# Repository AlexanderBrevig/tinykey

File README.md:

# tinykey

A project just for fun, to see if I can type on it.

## The rough idea

The layout:

```
↑ ◐ ● ◑ ↹ ⌫      ↩ ␣ ◐ ● ◑ ↓
```

Imagine mapping the home row `ASDFG` to three keys, using chords.
Let's say we only have the `SDF` keys, the mapping will be like this:

```
S = A
SD = S
D = D
DF = F
F = G
```

So, if you wanted to type `SAD` then you would press `SD` `S` `D`. The grouped keys becomes a chord for your ring and middle finger.
Now then, what if you wanted to type `FEAST`?

Notice that `↑` on the pinky? It shifts the home row up.
Before things get crazy, let's rename `SDF` to `◐●◑`.

Now, then `FEAST` becomes:

```
F  E  A S  T
●◑ ↑● ● ◐● ↑◑ 
```

The same applies for the `↓` on the right pinky. This shifts the home row down.

So what about the thumbs then?

The left thumb has two keys, a TAB `↹` and a BACKSPACE `⌫`. 
The right thumb has RETURN `↩` and SPACE `␣`.
However, when held they enter other layers.

In my (still only slideware) config, I've mapped the numbers to the top row on the SPACE layer.
So, for me to type out `1337` it would be:

```
1   3   3   7
↑◐␣ ↑●␣ ↑●␣ ↑␣●◑
```

I will post my complete keymap when it's ready.

## Taking it further

We could also realize five keys by using timing and only two keys.

```
A S   D  F   G
◐ ◐-◑ ◑◐ ◑-◐ ◑
```

S and F has a roll, while D is _at the same time_ (within a confurable Δt ms).

Will try to play with this as well, and thus getting the layout down to 10 keys total.

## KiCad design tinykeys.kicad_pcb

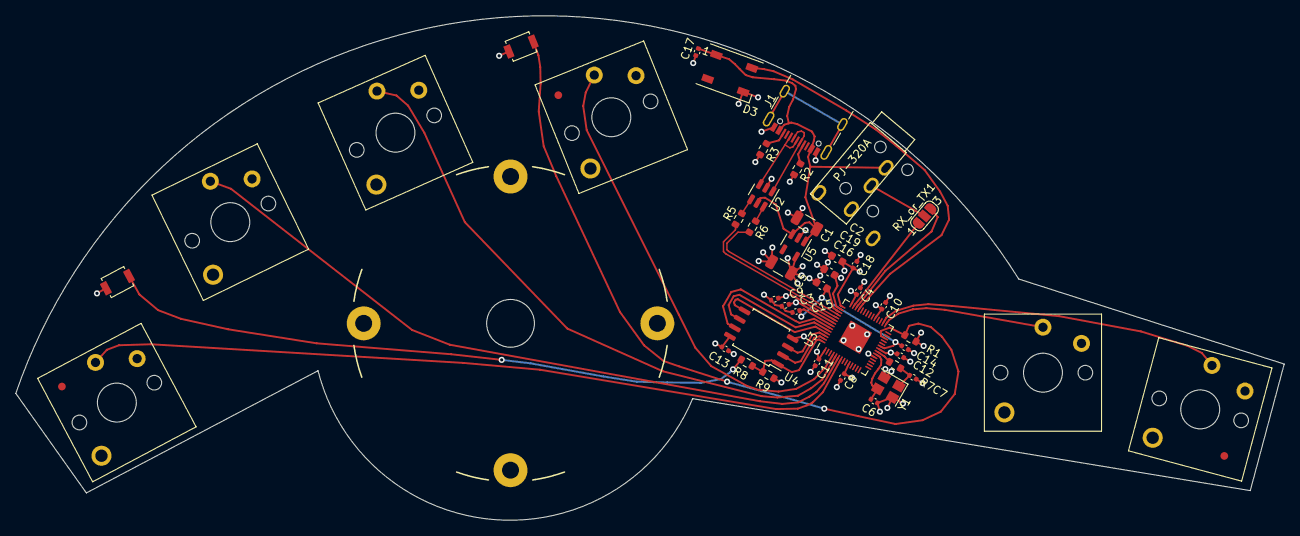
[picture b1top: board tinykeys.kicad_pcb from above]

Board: 4 copper layers, 164.6 x 65.4 mm, 48 parts (0 on the bottom side), 33 nets.

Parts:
BOOT1: TACT; SW_SPST_B3U-1000P
C1: DNP; C_1206_3216Metric
C2, C16, C19: 1u; C_0603_1608Metric
C3, C4, C8, C9, C10, C11, C12, C13, C14, C15, C17, C18: 100n; C_0402_1005Metric
C5: 1u; C_1206_3216Metric
C6, C7: 15p; C_0402_1005Metric
D3: WS2812B; LED_WS2812B_PLCC4_5.0x5.0mm_P3.2mm
FID1, FID2, FID3: Fiducial; dualfiducial
H1: MountingHole_Pad; Tenting_Puck
INDEX1: SW; SW_Kailh_Choc_V1V2_1.00u
J1: USB_C_Receptacle_USB2.0; USB_C_Receptacle_GCT_USB4105-xx-A_16P_TopMnt_Horizontal
J2: AudioJack4; TRRS-PJ-320A
MIDDLE1: SW; SW_Kailh_Choc_V1V2_1.00u
PINKY1: SW; SW_Kailh_Choc_V1V2_1.00u
R1, R9: 10k; R_0603_1608Metric
R2, R3: 5K1; R_0603_1608Metric
R5, R6: 27R; R_0603_1608Metric
R7, R8: 1k; R_0603_1608Metric
RESET1: TACT; SW_SPST_B3U-1000P
RING1: SW; SW_Kailh_Choc_V1V2_1.00u
RX_or_TX1: Jumper_3_Open; SolderJumper-3_P1.3mm_Open_RoundedPad1.0x1.5mm_NumberLabels
TFAR1: SW; SW_Kailh_Choc_V1V2_1.00u
TNEAR1: SW; SW_Kailh_Choc_V1V2_1.00u
U2: USBLC6-2SC6; SOT-23-6
U3: RP2040; QFN-56-1EP_7x7mm_P0.4mm_EP3.2x3.2mm
U4: W25Q128JVS; SOIC-8_5.23x5.23mm_P1.27mm
U5: TLV70033DDCR; SOT-23-5
Y1: 12MHz; Crystal_SMD_3225-4Pin_3.2x2.5mm

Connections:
+1V1: C14.1, C15.1, C16.1, U3.23 (DVDD), U3.45 (VREG_VOUT), U3.50 (DVDD)
+3V3: C2.1, C3.1, C4.1, C5.1, C8.1, C9.1, C10.1, C11.1, C12.1, C13.1, C18.1, C19.1, R1.1, R9.1, U3.1 (IOVDD), U3.10 (IOVDD), U3.22 (IOVDD), U3.33 (IOVDD), U3.42 (IOVDD), U3.43 (ADC_AVDD), U3.44 (VREG_IN), U3.48 (USB_VDD), U3.49 (IOVDD), U4.8 (VCC), U5.5 (OUT)
BOOT: BOOT1.2, R8.1
GND: BOOT1.1, C1.2, C2.2, C3.2, C4.2, C5.2, C6.1, C7.1, C8.2, C9.2, C10.2, C11.2, C12.2, C13.2, C14.2, C15.2, C16.2, C17.2, C18.2, C19.2, D3.3 (VSS), H1.1, INDEX1.2, J1.A1 (GND), J1.A12 (GND), J1.B1 (GND), J1.B12 (GND), J2.S, J2.T, MIDDLE1.2, PINKY1.2, R2.2, R3.2, RESET1.1, RING1.2, TFAR1.2, TNEAR1.2, U2.2 (GND), U3.19 (TESTEN), U3.57 (GND), U4.4 (GND), U5.2 (GND), Y1.2, Y1.4
INDEX: INDEX1.1, U3.4 (GPIO2)
MIDDLE: MIDDLE1.1, U3.5 (GPIO3)
unnamed: C7.2, R7.1, Y1.1
unnamed: J1.A5 (CC1), R2.1
unnamed: J1.B5 (CC2), R3.1
unnamed: J2.R1, RX_or_TX1.2 (C)
unnamed: C6.2, U3.20 (XIN), Y1.3
unnamed: R7.2, U3.21 (XOUT)
PINKY: PINKY1.1, U3.7 (GPIO5)
QSPI_SCLK: U3.52 (QSPI_SCLK), U4.6 (CLK)
QSPI_SD0: U3.53 (QSPI_SD0), U4.5 (DI(IO0))
QSPI_SD1: U3.55 (QSPI_SD1), U4.2 (DO(IO1))
QSPI_SD2: U3.54 (QSPI_SD2), U4.3 (IO2)
QSPI_SD3: U3.51 (QSPI_SD3), U4.7 (IO3)
QSPI_~SS: R8.2, R9.2, U3.56 (QSPI_SS), U4.1 (~CS)
RING: RING1.1, U3.6 (GPIO4)
RUN: R1.2, RESET1.2, U3.26 (RUN)
STATUS_LED: D3.4 (DIN), U3.39 (GPIO27_ADC1)
TFAR: TFAR1.1, U3.30 (GPIO19)
TNEAR: TNEAR1.1, U3.29 (GPIO18)
UART0_RX: RX_or_TX1.1 (A), U3.41 (GPIO29_ADC3)
UART0_TX: RX_or_TX1.3 (B), U3.40 (GPIO28_ADC2)
USB_D+: R5.1, U2.4 (I/O2)
USB_D-: R6.1, U2.6 (I/O1)
USB_FIL_D+: R5.2, U3.47 (USB_DP)
USB_FIL_D-: R6.2, U3.46 (USB_DM)
USB_RAW_D+: J1.A6 (D+), J1.B6 (D+), U2.3 (I/O2)
USB_RAW_D-: J1.A7 (D-), J1.B7 (D-), U2.1 (I/O1)
VBUS: C1.1, C17.1, D3.1 (VDD), J1.A4 (VBUS), J1.A9 (VBUS), J1.B4 (VBUS), J1.B9 (VBUS), J2.R2, U2.5 (VBUS), U5.1 (IN), U5.3 (EN)

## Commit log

2023-08-07 feat: initial commit, ordered rev 1
2023-08-07 docs: add illustration
2023-08-07 docs: note about a two key home row
2023-08-07 docs: remove superfluous symbols
2023-08-08 docs: fix taking it further example
